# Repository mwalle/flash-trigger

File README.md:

# Tiny LED Trigger

Your simple, cheap and open LED flash trigger for your underwater strobe.

## Features

The flash trigger provides the following features:

- Reliably triggers your optical underwater strobe in manual mode.
- Converts any trigger pulse from your camera to a constant 100µs LED
  pulse.
- Very bright pulse because the LED is driven with a very high current
  (most LEDs have a peak forward current of 100mA-150mA specified for
  100µs for a 1/10 duty cycle).
- Pre-flash supression mode. Useful if your camera has a pre-flash pulse on
  the hot shoe pin.
- Powered by just one CR2032 coin cell.
- More than 10.000 cycles per coin cell.
- Five different positions for the LED.
- Supports up to two LEDs in parallel.
- Battery good indication.
- Extremely small.
- [Open Hardware](https://certification.oshwa.org/de000130.html),
  schematics and layout are free for everyone.

## Pictures

## Schematics
The LED trigger consists of:
 - the [base board](flash-trigger/flash-trigger.pdf) and
 - a [Canon compatible hot shoe](canon-hotshoe/canon-hotshoe.pdf).

Only populate the X pin of the hot shoe to be compatible with any camera.

## Theory Of Operation

At the heart of the circuit, there is a monostable multivibrator (`U1B`)
which converts any falling edge of the trigger output of your camera to a
constant length pulse of about 100µs. The time constant is given by the
values of `C1` and `R3`. The multivibrator is retriggerable, thus if there
would be a second falling edge within that 100µs pulse the period would
start over. But in practice, this shouldn't matter.

A second monostable multivibrator (`U1A`) can be used to supress a
pre-flash pulse. In this case, the second input of `U1B` is connected to
the output of `U1A` and only if that output is active the 100µs pulse is
generated. The output of `U1A` in turn, will be active for about 100ms
after a *rising* edge of the flash trigger input. Thus the sequence is as
follows:
 1. The camera pulses the trigger output low to generate a pre-flash.
 2. Normally, `U1B` would now trigger a pulse on the falling edge, but
	because the second input is still inactive, no pulse is generated.
 3. On the rising edge (that is, at the end of the pre-flash pulse), `U1A`
	triggers a 100ms pulse and arm `U1B`.
 4. The camera triggers the actual main flash by pulsing the output trigger
	again.
 5. This time, the second input of `U1B` is active and the 100µs trigger
	pulse will be generated.

This has the following two implications:
 * The duration between pre-flash and the main flash must not exceed 100ms.
 * Repeated flashes will be limited to about 10Hz (reciprocal value of the
   100ms)

Both shouldn't really matter. But of course you can tune this time constant
by changing the values of `C3` and `R9`.

The 100µs pulse is enabling the logic level N-channel MOSFET `Q1`, which is
driving the LEDs `D1`..`D5` through individual series resistors `R1`..`R5`.
Depending on the value of the series resistor and the LEDs, it should be
possible to connect up to two LEDs.

The circuit is designed to work down to the forward voltage of the LED.
`U1` will work down to 1.0V. Nevertheless, there is a voltage supervisor,
which is pretty simple: `U2` will pull its output to high if its supply
voltage is greater than 2.7V, thus driving the green LED `D6` with its
series resistor `R11`. At 2.7V the coin cell should still have about 25% of
its capacity, giving the user enough margin.

## Trigger LEDs

The flash trigger has five different LED positions facing left to right.
It should be possible to populate up to two LEDs. The LEDs should be chosen
according to the flash you like to use. The author has successfully tried
red and infrared LEDs with INON flashes. The more the LED is towards the
infrared spectrum, the lower is its forward voltage and the longer it will
work with a given coin cell.

## Bill Of Materials

| Ref | Qty | Part | Footprint |
| --- | --- | --- | --- |
| R1, R2, R3, R4, R5, R6 | 6 | 10Ω Resistor | 0603 |
| R7, R8, R10 | 3 | 100kΩ Resistor | 0603 |
| R9 | 1 | 1MΩ Resistor | 0603 |
| R11, R12 | 2 | 1.5kΩ Resistor | 0603 |
| C1 | 1 | 10nF Ceramic Capacitor | 0603 |
| C2 | 1 | 100µF Ceramic Capacitor | 0805 |
| C3 | 1 | 200nF Ceramic Capacitor | 0603 |
| C4 | 1 | 2.2nF Ceramic Capacitor | 0603 |
| C5 | 1 | 100pF Ceramic Capacitor | 0603 |
| D1, D2, D3, D4, D5 | 5 | LED | THT |
| D6 | 1 | Green LED | 0603 |
| Q1 | 1 | NDS331N N-Channel MOSFET | SOT23-3 |
| U1 | 1 | 74LV123 Dual Retriggerable Monostable Multivibrator | SSOP16 |
| U2 | 1 | BD49K27G Voltage Supervisor 2.7V | SSOP3 |
| SW1 | 1 | PCM12 Switch | - |
| SW2 | 1 | PTS810 Push Button | - |
| BT1 | 1 | CR2032 Coin Cell Holder | - |
| J1, J2 | 2 | MillMax 0550 Pin Receptable | - |
| J3, J4 | 2 | MillMax 0508 PCB Pin | - |

## Kits and PCBs

If you need a PCB, a kit or maybe an assembled board, contact me at
<flash-trigger@walle.cc>.

## License

This source describes Open Hardware and is licensed under the CERN-OHL-S
v2.

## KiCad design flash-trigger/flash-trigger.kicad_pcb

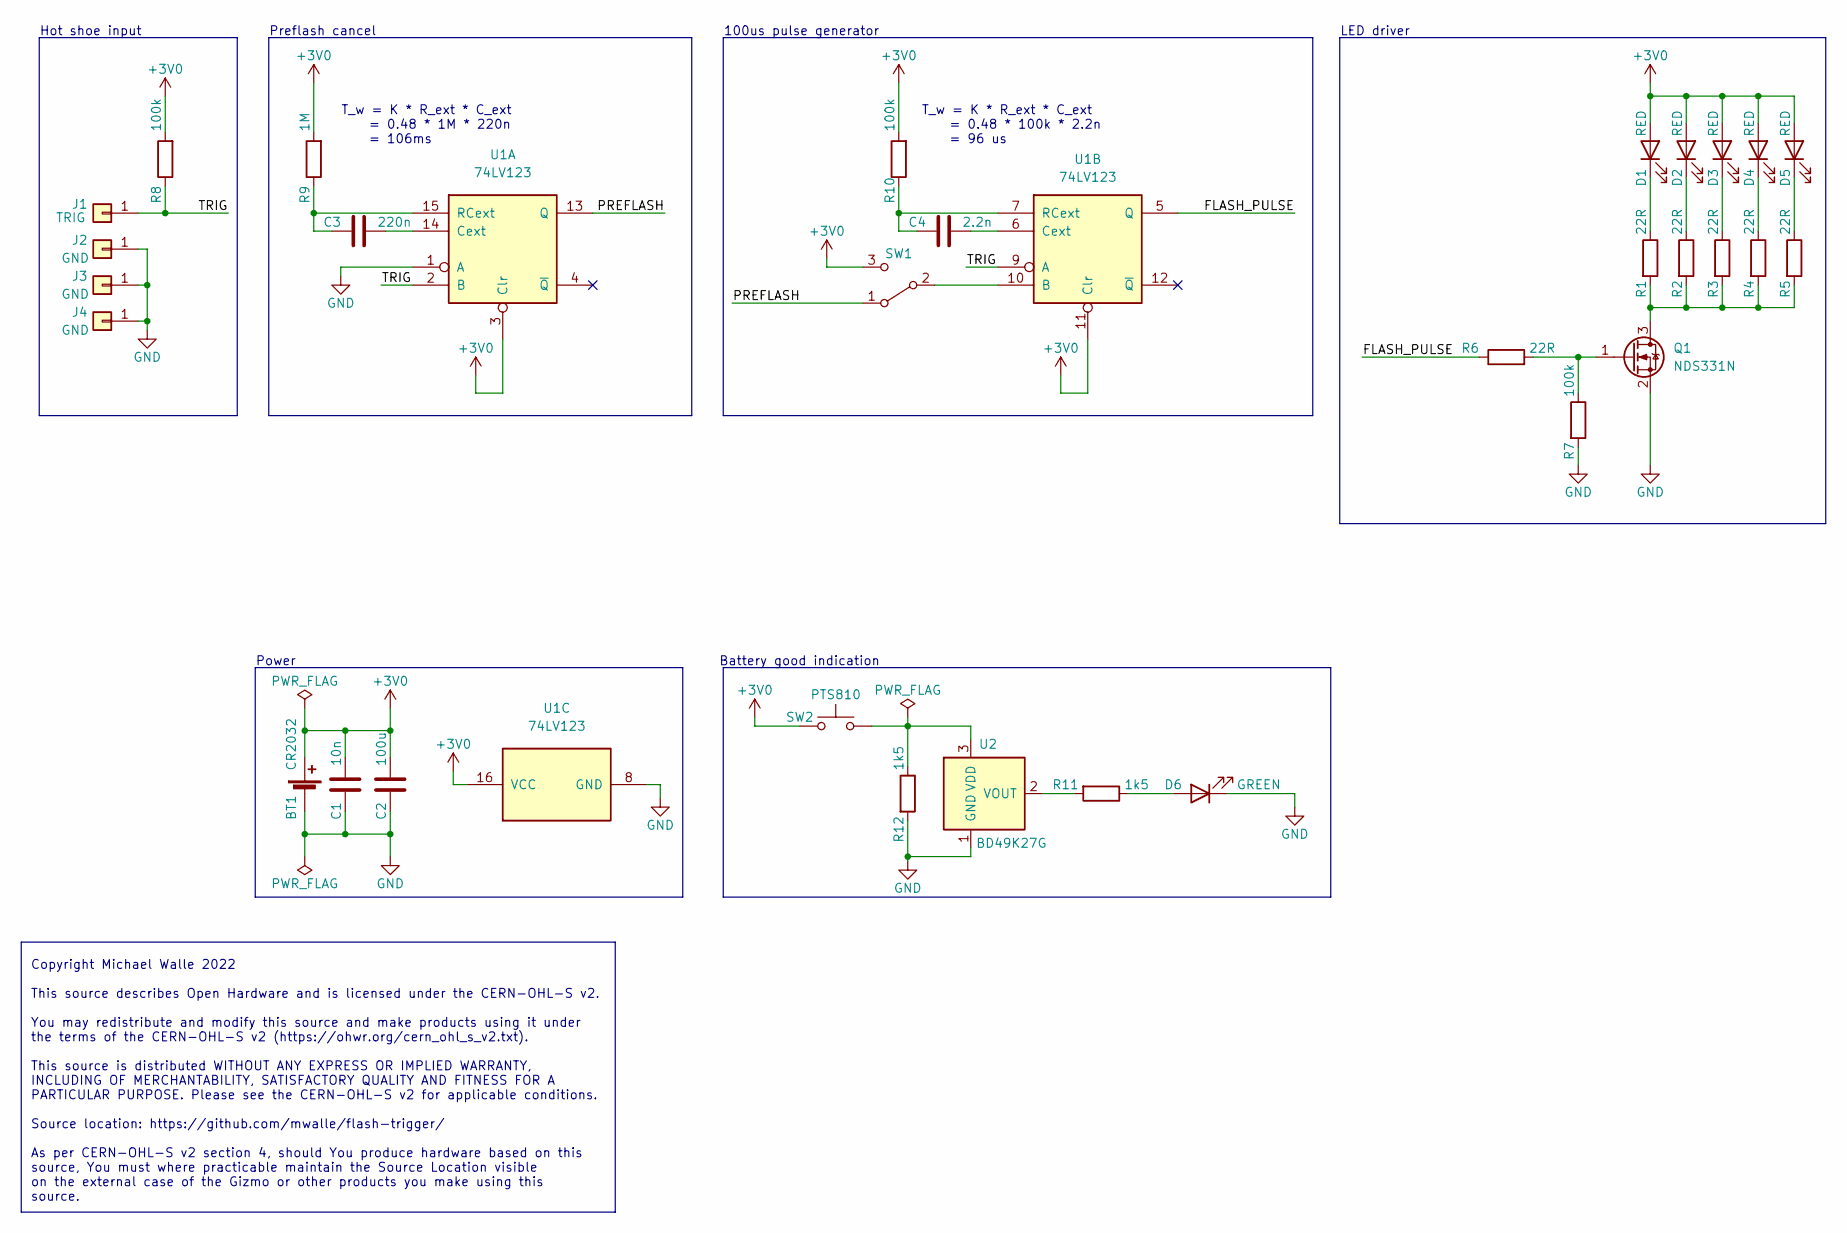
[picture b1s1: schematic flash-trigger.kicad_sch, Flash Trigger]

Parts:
BT1: CR2032; BatteryHolder_Keystone_2899_1x2032
C1: 10n; C_0603_1608Metric_Pad1.08x0.95mm_HandSolder
C2: 100u; C_0805_2012Metric_Pad1.18x1.45mm_HandSolder
C3: 220n; C_0603_1608Metric_Pad1.08x0.95mm_HandSolder
C4: 2.2n; C_0603_1608Metric_Pad1.08x0.95mm_HandSolder
D1, D2, D3, D4, D5: RED; LED_D5.0mm_Horizontal_O3.81mm_Z3.0mm
D6: GREEN; LED_0603_1608Metric_Pad1.05x0.95mm_HandSolder
J1: TRIG; 0550_52mil
J2: GND; 0550_52mil
J3, J4: GND; 0508_20mil
Q1: NDS331N; SOT-23_Handsoldering
R1, R2, R3, R4, R5, R6: 22R; R_0603_1608Metric_Pad0.98x0.95mm_HandSolder
R7, R8, R10: 100k; R_0603_1608Metric_Pad0.98x0.95mm_HandSolder
R9: 1M; R_0603_1608Metric_Pad0.98x0.95mm_HandSolder
R11, R12: 1k5; R_0603_1608Metric_Pad0.98x0.95mm_HandSolder
SW1: PCM12; SW_SPDT_PCM12
SW2: PTS810; SW_SPST_PTS810
U1: 74LV123; SSOP-16_4.4x5.2mm_P0.65mm
U2: BD49K27G; SOT-23_Handsoldering

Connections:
+3V0: BT1.1 (+), C1.1, C2.1, D1.2 (A), D2.2 (A), D3.2 (A), D4.2 (A), D5.2 (A), R8.2, R9.2, R10.2, SW1.3 (C), SW2.1, U1.3 (Clr), U1.11 (Clr), U1.16 (VCC)
/FLASH_PULSE: R6.1, U1.5 (Q)
/PREFLASH: SW1.1 (A), U1.13 (Q)
/TRIG: J1.1, R8.1, U1.2 (B), U1.9 (A)
GND: BT1.2 (-), C1.2, C2.2, D6.1 (K), J2.1, J3.1, J4.1, Q1.2 (S), R7.2, R12.2, U1.1 (A), U1.8 (GND), U2.1 (GND)
unnamed: C3.1, U1.14 (Cext)
unnamed: C3.2, R9.1, U1.15 (RCext)
unnamed: C4.1, U1.6 (Cext)
unnamed: C4.2, R10.1, U1.7 (RCext)
unnamed: D1.1 (K), R1.1
unnamed: D2.1 (K), R2.1
unnamed: D3.1 (K), R3.1
unnamed: D4.1 (K), R4.1
unnamed: D5.1 (K), R5.1
unnamed: D6.2 (A), R11.1
unnamed: Q1.1 (G), R6.2, R7.1
unnamed: Q1.3 (D), R1.2, R2.2, R3.2, R4.2, R5.2
unnamed: R11.2, U2.2 (VOUT)
unnamed: R12.1, SW2.2, U2.3 (VDD)
unnamed: SW1.2 (B), U1.10 (B)

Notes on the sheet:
100us pulse generator
Battery good indication
T_w = K * R_ext * C_ext = 0.48 * 100k * 2.2n = 96 us
Power
Copyright Michael Walle 2022 This source describes Open Hardware and is licensed under the CERN-OHL-S v2. You may redistribute and modify this source and make products using it under the terms of the CERN-OHL-S v2 (https://ohwr.org/cern_ohl_s_v2.txt). This source is distributed WITHOUT ANY EXPRESS 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
Hot shoe input
LED driver
T_w = K * R_ext * C_ext = 0.48 * 1M * 220n = 106ms
Preflash cancel

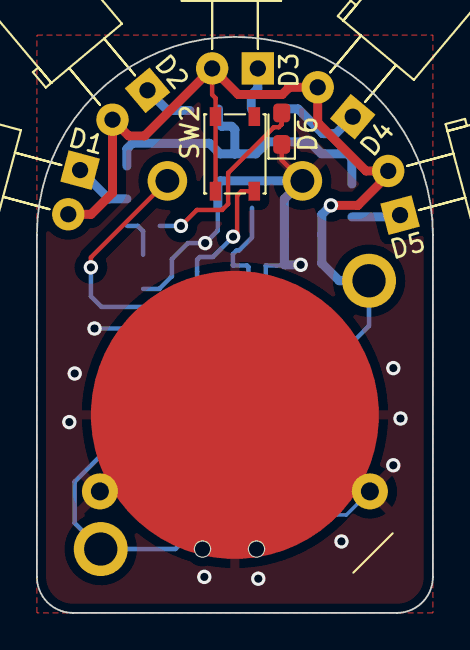
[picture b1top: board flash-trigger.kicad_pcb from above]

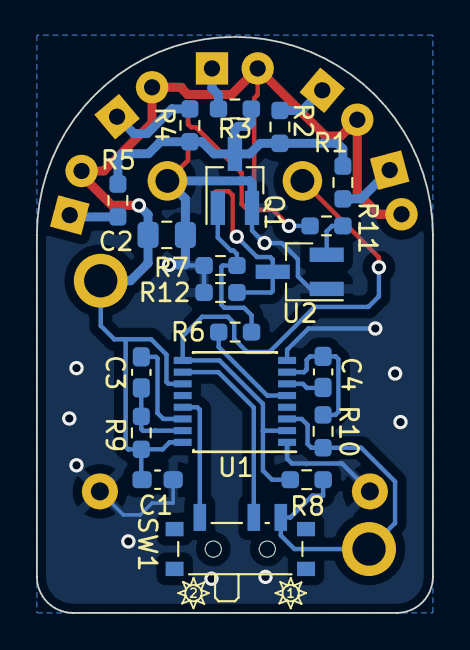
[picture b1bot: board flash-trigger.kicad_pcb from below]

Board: 2 copper layers, 22.0 x 32.0 mm, 32 parts (24 on the bottom side), 20 nets.

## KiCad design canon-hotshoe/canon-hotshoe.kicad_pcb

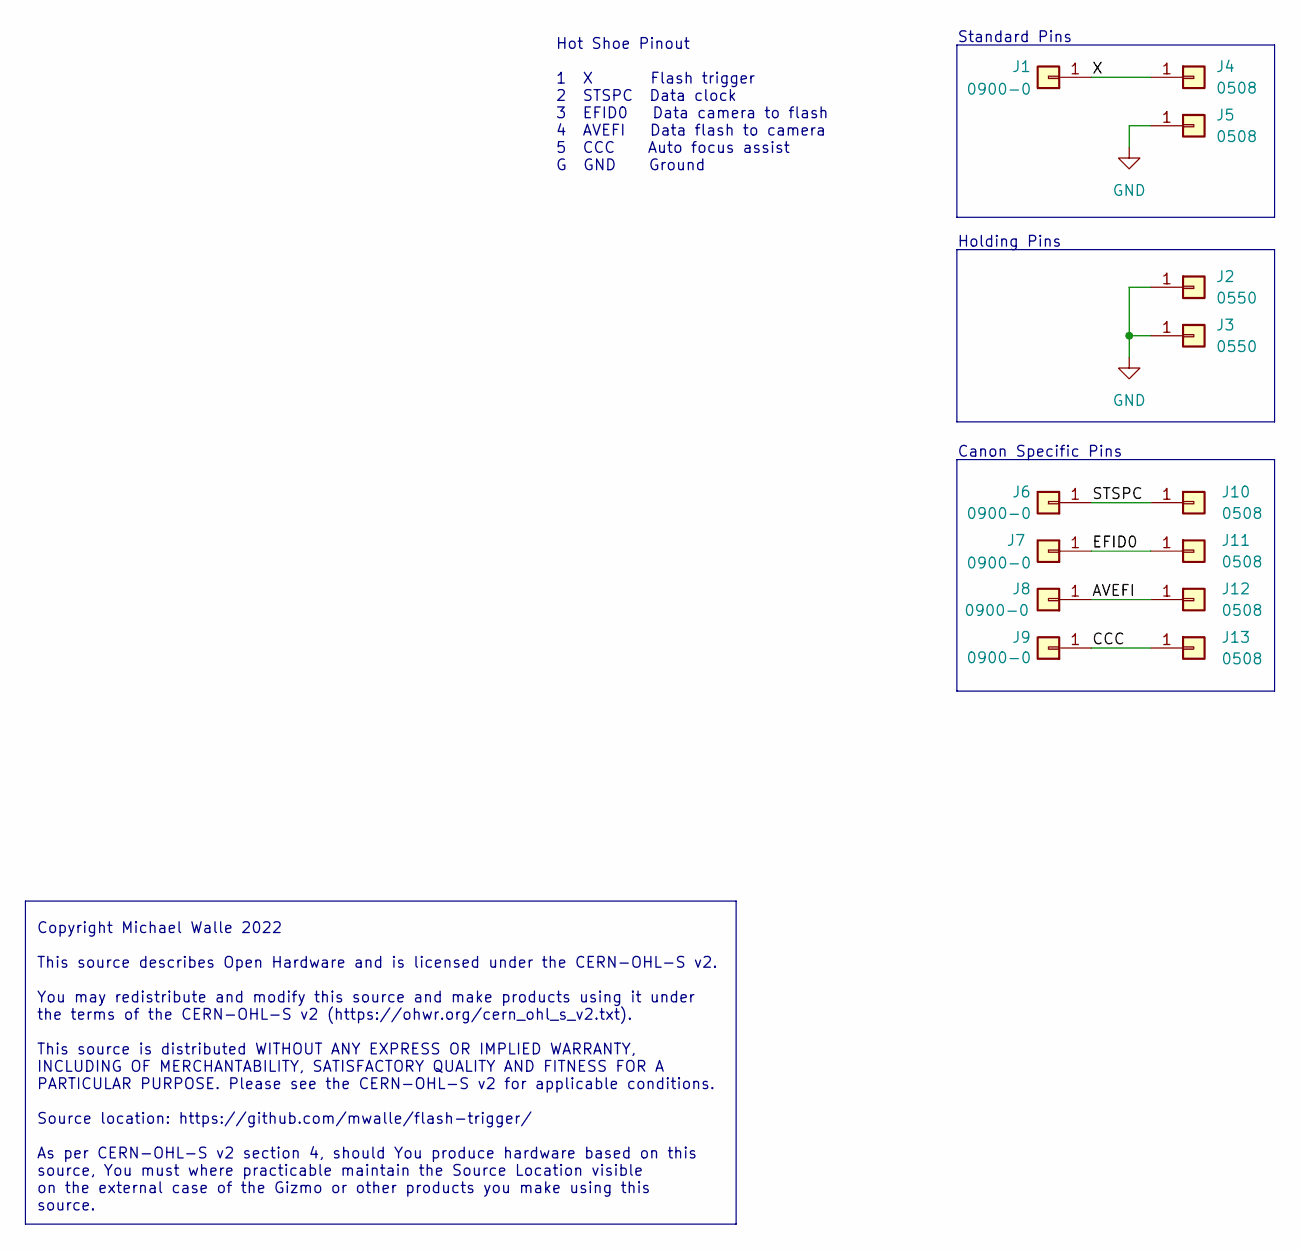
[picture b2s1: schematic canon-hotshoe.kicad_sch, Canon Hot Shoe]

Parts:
J1, J6, J7, J8, J9: 0900-0; 0900-0_137mil_Reverse
J2, J3: 0550; 0550_52mil
J4, J5, J10, J11, J12, J13: 0508; 0508_20mil

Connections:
/AVEFI: J8.1, J12.1
/CCC: J9.1, J13.1
/EFID0: J7.1, J11.1
/STSPC: J6.1, J10.1
/X: J1.1, J4.1
GND: J2.1, J3.1, J5.1

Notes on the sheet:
Holding Pins
Standard Pins
Hot Shoe Pinout 1 X Flash trigger 2 STSPC Data clock 3 EFID0 Data camera to flash 4 AVEFI Data flash to camera 5 CCC Auto focus assist G GND Ground
Copyright Michael Walle 2022 This source describes Open Hardware and is licensed under the CERN-OHL-S v2. You may redistribute and modify this source and make products using it under the terms of the CERN-OHL-S v2 (https://ohwr.org/cern_ohl_s_v2.txt). This source is distributed WITHOUT ANY EXPRESS 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
Canon Specific Pins

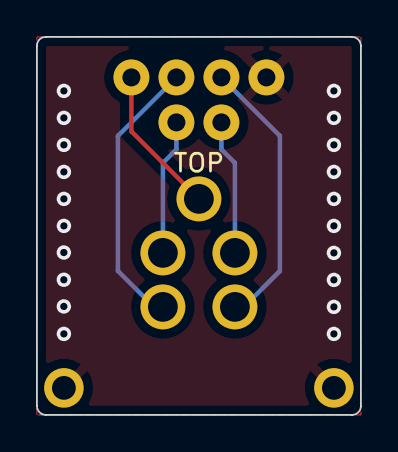
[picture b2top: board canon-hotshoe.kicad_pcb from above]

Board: 2 copper layers, 18.0 x 21.0 mm, 13 parts (0 on the bottom side), 6 nets.

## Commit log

2022-11-22 Fixes and improvements
    * fix the preflash detection
    * clean the canon hot shoe schematics up
    * enlarge the hotshoe pcb and place two new mounting pins
    * change the battery low to a battery good detection
    * move the supervisor ic away from the hot shoe rail
    * use a longer pogo pin
2022-11-22 flash-trigger: Drop RC circuit and improve layout
2022-11-22 Renumber RefDes and add OSHW logo and URL
2022-11-22 Prepare rev2.0
2022-11-22 flash-trigger: replace BD49KxxG with BD49K27G
    We use a 2.7V voltage supervisor.
2022-11-22 canon-hotshoe: exclude OSHW symbol from schematics
2022-11-22 schematics: Fix the battery good title
    Since rev2 this is now a battery good detection.
2022-11-22 flash-trigger: Increase C2 to 100uF
2022-11-22 Add intial README
2022-11-22 flash-trigger: Update value of SW2
    Reflect the actual component value instead of its function.
2022-11-22 Prepare rev2.1
2022-12-13 README: add pictures, OSHW cert logo and misc
2023-01-08 README: add more pictures
2023-01-08 README: decrease preview images size
    So three will fit into one row.

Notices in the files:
canon-hotshoe/canon-hotshoe.kicad_sch:
As per CERN-OHL-S v2 section 4, should You produce hardware based on this
